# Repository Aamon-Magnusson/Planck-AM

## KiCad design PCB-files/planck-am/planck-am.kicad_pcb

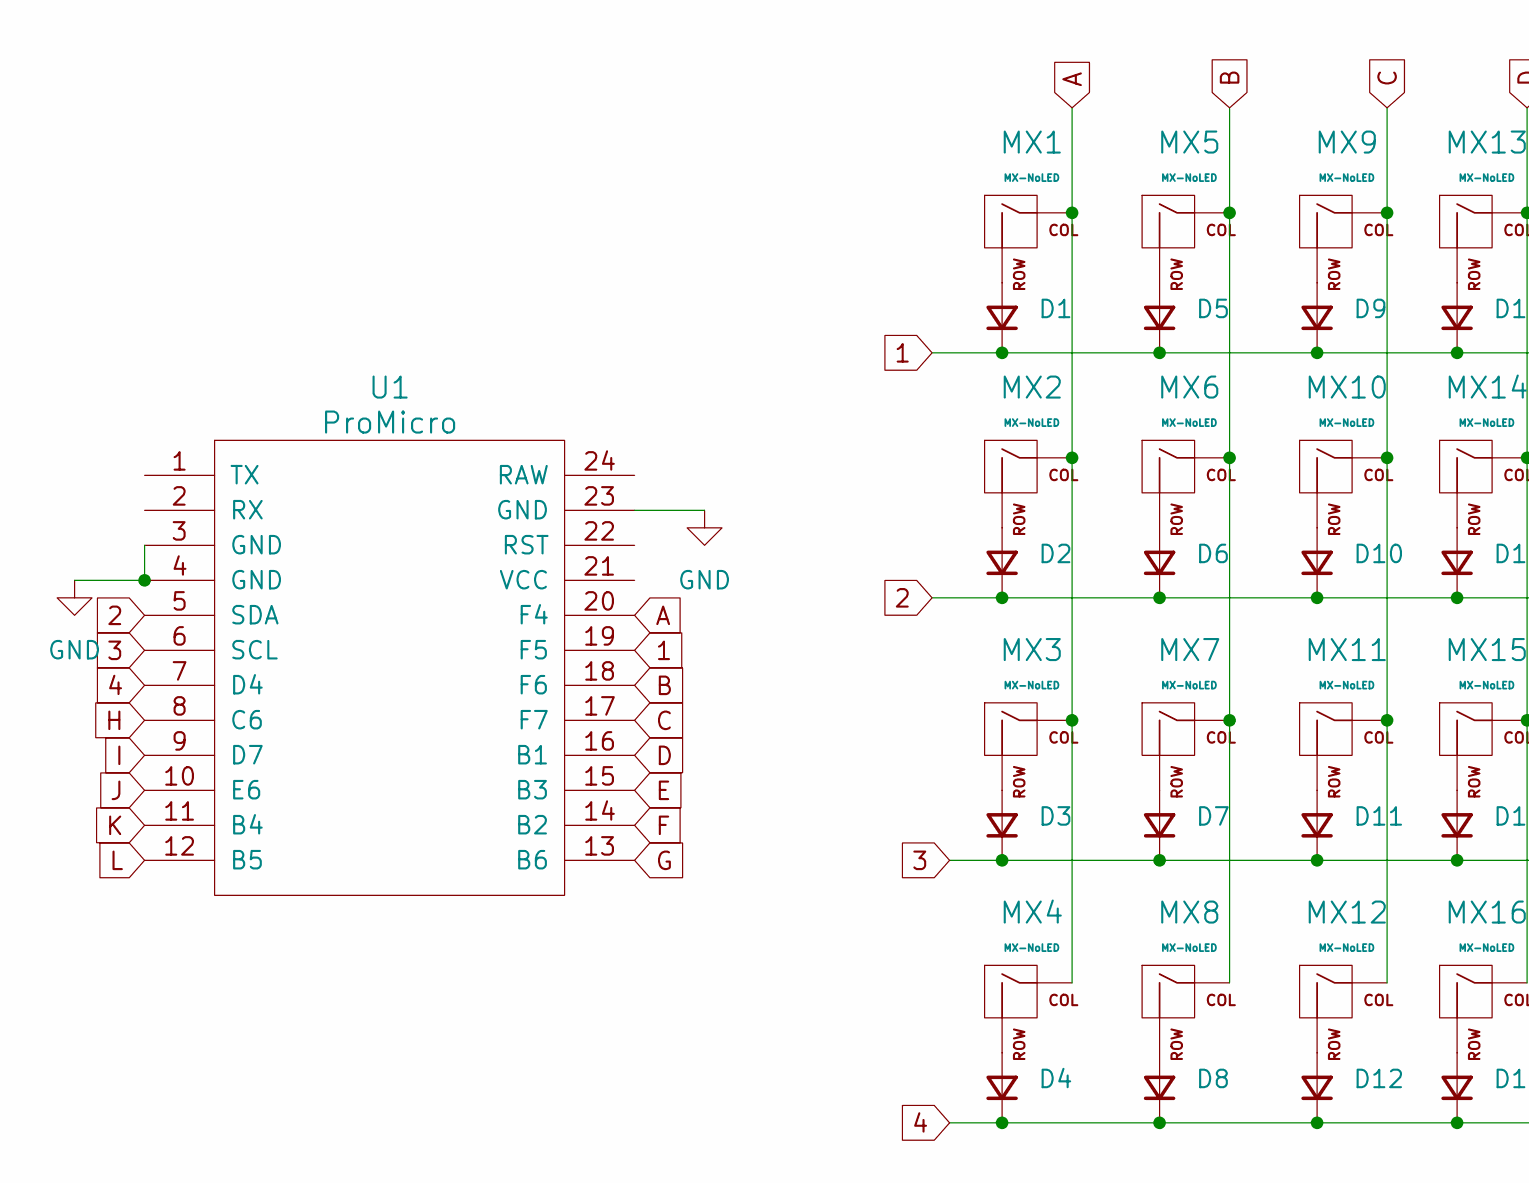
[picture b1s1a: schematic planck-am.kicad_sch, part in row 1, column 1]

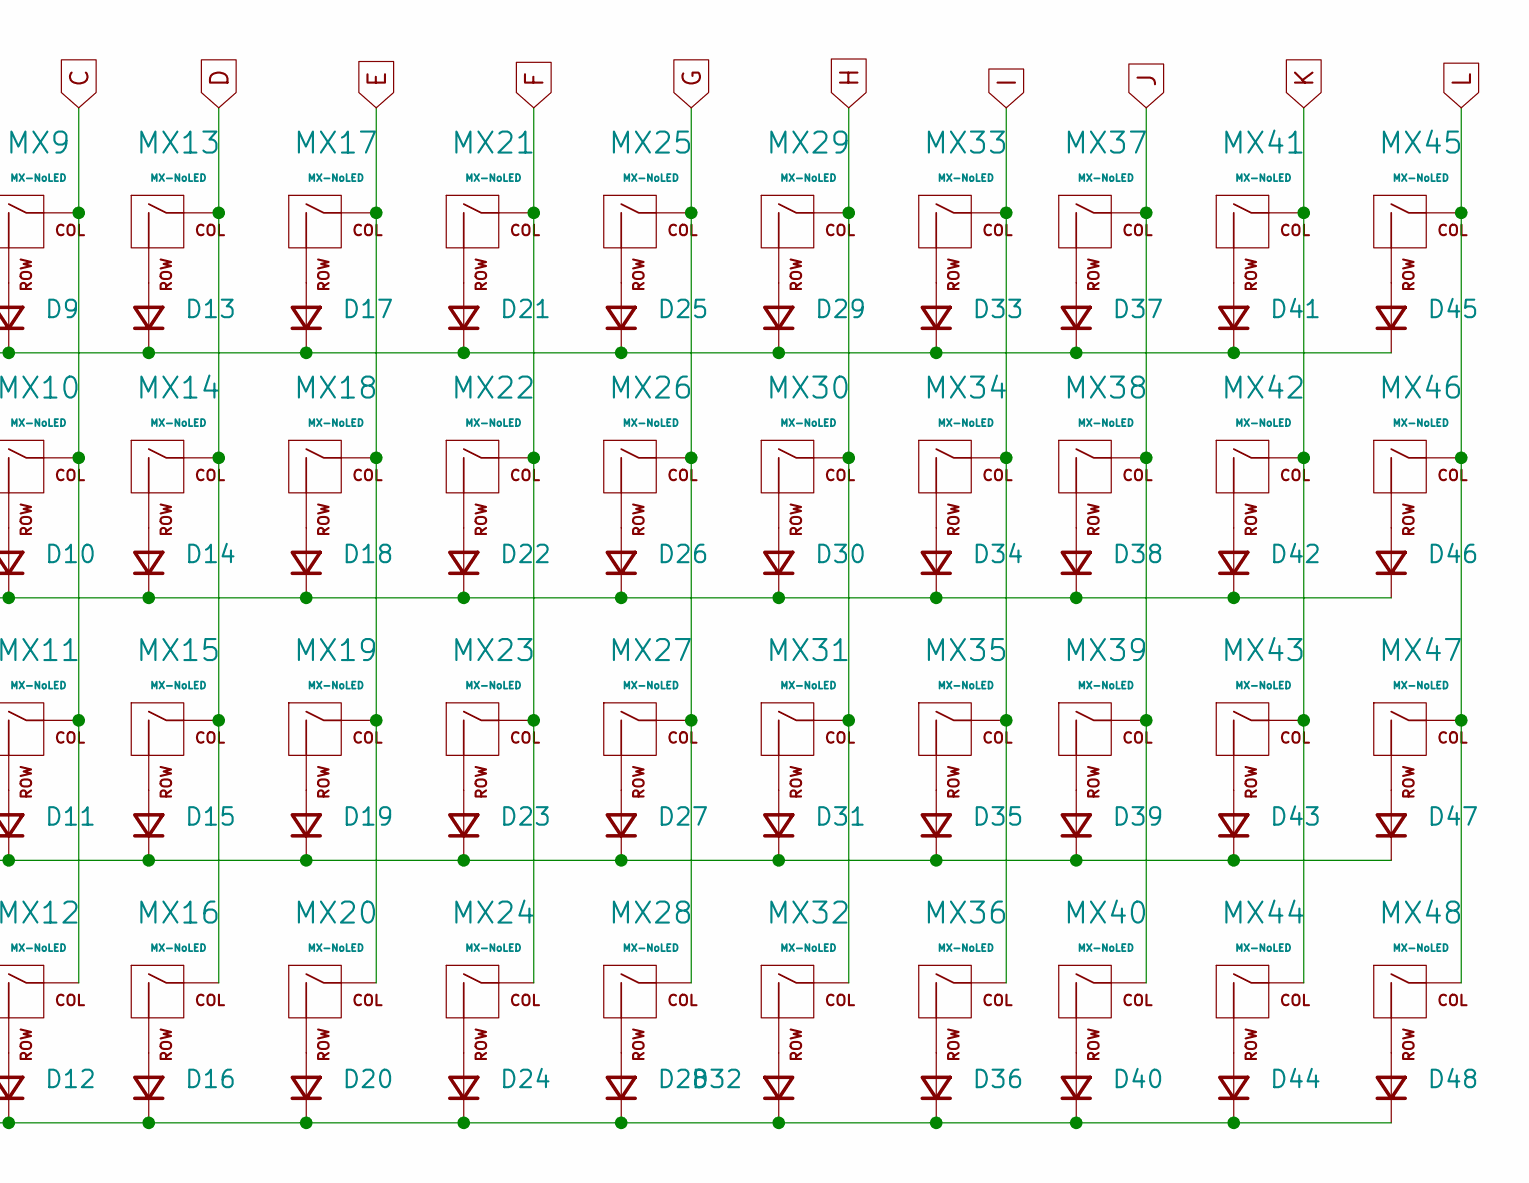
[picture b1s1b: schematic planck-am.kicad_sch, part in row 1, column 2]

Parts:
D1, D2, D3, D4, D5, D6, D7, D8, D9, D10, D11, D12, D13, D14, D15, D16, D17, D18, D19, D20, D21, D22, D23, D24, D25, D26, D27, D28, D29, D30, D31, D32, D33, D34, D35, D36, D37, D38, D39, D40, D41, D42, D43, D44, D45, D46, D47, D48: D_Small; D_SOD-123
MX1, MX2, MX3, MX4, MX5, MX6, MX7, MX8, MX9, MX10, MX11, MX12, MX13, MX14, MX15, MX16, MX17, MX18, MX19, MX20, MX21, MX22, MX23, MX24, MX25, MX26, MX27, MX28, MX29, MX30, MX31, MX32, MX33, MX34, MX35, MX36, MX37, MX38, MX39, MX40, MX41, MX42, MX43, MX44, MX45, MX46, MX47, MX48: MX-NoLED; MXOnly-1U-Hotswap
U1: ProMicro

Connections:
1: D1.1 (K), D5.1 (K), D9.1 (K), D13.1 (K), D17.1 (K), D21.1 (K), D25.1 (K), D29.1 (K), D33.1 (K), D37.1 (K), D41.1 (K), D45.1 (K), U1.19 (F5)
2: D2.1 (K), D6.1 (K), D10.1 (K), D14.1 (K), D18.1 (K), D22.1 (K), D26.1 (K), D30.1 (K), D34.1 (K), D38.1 (K), D42.1 (K), D46.1 (K), U1.5 (SDA)
3: D3.1 (K), D7.1 (K), D11.1 (K), D15.1 (K), D19.1 (K), D23.1 (K), D27.1 (K), D31.1 (K), D35.1 (K), D39.1 (K), D43.1 (K), D47.1 (K), U1.6 (SCL)
4: D4.1 (K), D8.1 (K), D12.1 (K), D16.1 (K), D20.1 (K), D24.1 (K), D28.1 (K), D32.1 (K), D36.1 (K), D40.1 (K), D44.1 (K), D48.1 (K), U1.7 (D4)
A: MX1.1 (COL), MX2.1 (COL), MX3.1 (COL), MX4.1 (COL), U1.20 (F4)
B: MX5.1 (COL), MX6.1 (COL), MX7.1 (COL), MX8.1 (COL), U1.18 (F6)
C: MX9.1 (COL), MX10.1 (COL), MX11.1 (COL), MX12.1 (COL), U1.17 (F7)
D: MX13.1 (COL), MX14.1 (COL), MX15.1 (COL), MX16.1 (COL), U1.16 (B1)
E: MX17.1 (COL), MX18.1 (COL), MX19.1 (COL), MX20.1 (COL), U1.15 (B3)
F: MX21.1 (COL), MX22.1 (COL), MX23.1 (COL), MX24.1 (COL), U1.14 (B2)
G: MX25.1 (COL), MX26.1 (COL), MX27.1 (COL), MX28.1 (COL), U1.13 (B6)
GND: U1.3 (GND), U1.4 (GND), U1.23 (GND)
H: MX29.1 (COL), MX30.1 (COL), MX31.1 (COL), MX32.1 (COL), U1.8 (C6)
I: MX33.1 (COL), MX34.1 (COL), MX35.1 (COL), MX36.1 (COL), U1.9 (D7)
J: MX37.1 (COL), MX38.1 (COL), MX39.1 (COL), MX40.1 (COL), U1.10 (E6)
K: MX41.1 (COL), MX42.1 (COL), MX43.1 (COL), MX44.1 (COL), U1.11 (B4)
L: MX45.1 (COL), MX46.1 (COL), MX47.1 (COL), MX48.1 (COL), U1.12 (B5)
unnamed: D1.2 (A), MX1.2 (ROW)
unnamed: D2.2 (A), MX2.2 (ROW)
unnamed: D3.2 (A), MX3.2 (ROW)
unnamed: D4.2 (A), MX4.2 (ROW)
unnamed: D5.2 (A), MX5.2 (ROW)
unnamed: D6.2 (A), MX6.2 (ROW)
unnamed: D7.2 (A), MX7.2 (ROW)
unnamed: D8.2 (A), MX8.2 (ROW)
unnamed: D9.2 (A), MX9.2 (ROW)
unnamed: D10.2 (A), MX10.2 (ROW)
unnamed: D11.2 (A), MX11.2 (ROW)
unnamed: D12.2 (A), MX12.2 (ROW)
unnamed: D13.2 (A), MX13.2 (ROW)
unnamed: D14.2 (A), MX14.2 (ROW)
unnamed: D15.2 (A), MX15.2 (ROW)
unnamed: D16.2 (A), MX16.2 (ROW)
unnamed: D17.2 (A), MX17.2 (ROW)
unnamed: D18.2 (A), MX18.2 (ROW)
unnamed: D19.2 (A), MX19.2 (ROW)
unnamed: D20.2 (A), MX20.2 (ROW)
unnamed: D21.2 (A), MX21.2 (ROW)
unnamed: D22.2 (A), MX22.2 (ROW)
unnamed: D23.2 (A), MX23.2 (ROW)
unnamed: D24.2 (A), MX24.2 (ROW)
unnamed: D25.2 (A), MX25.2 (ROW)
unnamed: D26.2 (A), MX26.2 (ROW)
unnamed: D27.2 (A), MX27.2 (ROW)
unnamed: D28.2 (A), MX28.2 (ROW)
unnamed: D29.2 (A), MX29.2 (ROW)
unnamed: D30.2 (A), MX30.2 (ROW)
unnamed: D31.2 (A), MX31.2 (ROW)
unnamed: D32.2 (A), MX32.2 (ROW)
unnamed: D33.2 (A), MX33.2 (ROW)
unnamed: D34.2 (A), MX34.2 (ROW)
unnamed: D35.2 (A), MX35.2 (ROW)
unnamed: D36.2 (A), MX36.2 (ROW)
unnamed: D37.2 (A), MX37.2 (ROW)
unnamed: D38.2 (A), MX38.2 (ROW)
unnamed: D39.2 (A), MX39.2 (ROW)
unnamed: D40.2 (A), MX40.2 (ROW)
unnamed: D41.2 (A), MX41.2 (ROW)
unnamed: D42.2 (A), MX42.2 (ROW)
unnamed: D43.2 (A), MX43.2 (ROW)
unnamed: D44.2 (A), MX44.2 (ROW)
unnamed: D45.2 (A), MX45.2 (ROW)
unnamed: D46.2 (A), MX46.2 (ROW)
unnamed: D47.2 (A), MX47.2 (ROW)
unnamed: D48.2 (A), MX48.2 (ROW)

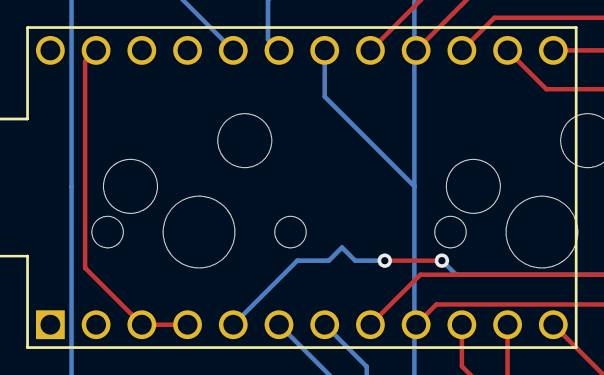
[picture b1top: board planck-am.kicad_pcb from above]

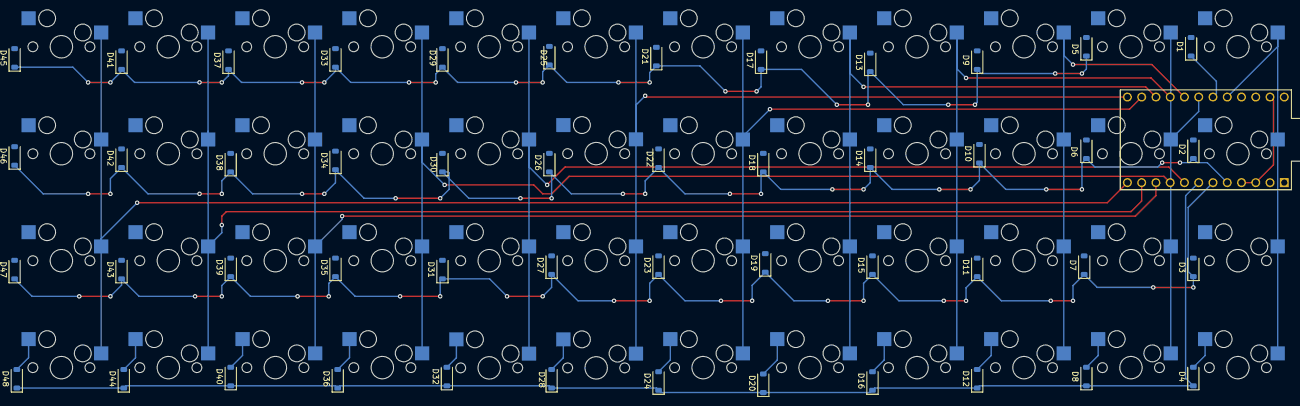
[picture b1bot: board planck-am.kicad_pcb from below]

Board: 2 copper layers, 97 parts (48 on the bottom side), 65 nets.

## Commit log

2023-02-19 Set up kicad with libraries for switches and pro micro
2023-02-19 Basic board layout
2023-02-19 Trying to get the layout set
2023-02-19 grid is good, need to get vias
2023-02-20 Got everything wired, not happy yet
2023-02-20 Revert "grid is good, need to get vias"
    This reverts commit afe9c75a0ba24579a276e137eadf1e0e1220068e.
2023-02-20 Revert "Got everything wired, not happy yet"
    This reverts commit 2e93da95e730097950f590344b8ece2b76e532c9.
2023-02-20 Ahhh
2023-02-20 Rewired the board, like it now
